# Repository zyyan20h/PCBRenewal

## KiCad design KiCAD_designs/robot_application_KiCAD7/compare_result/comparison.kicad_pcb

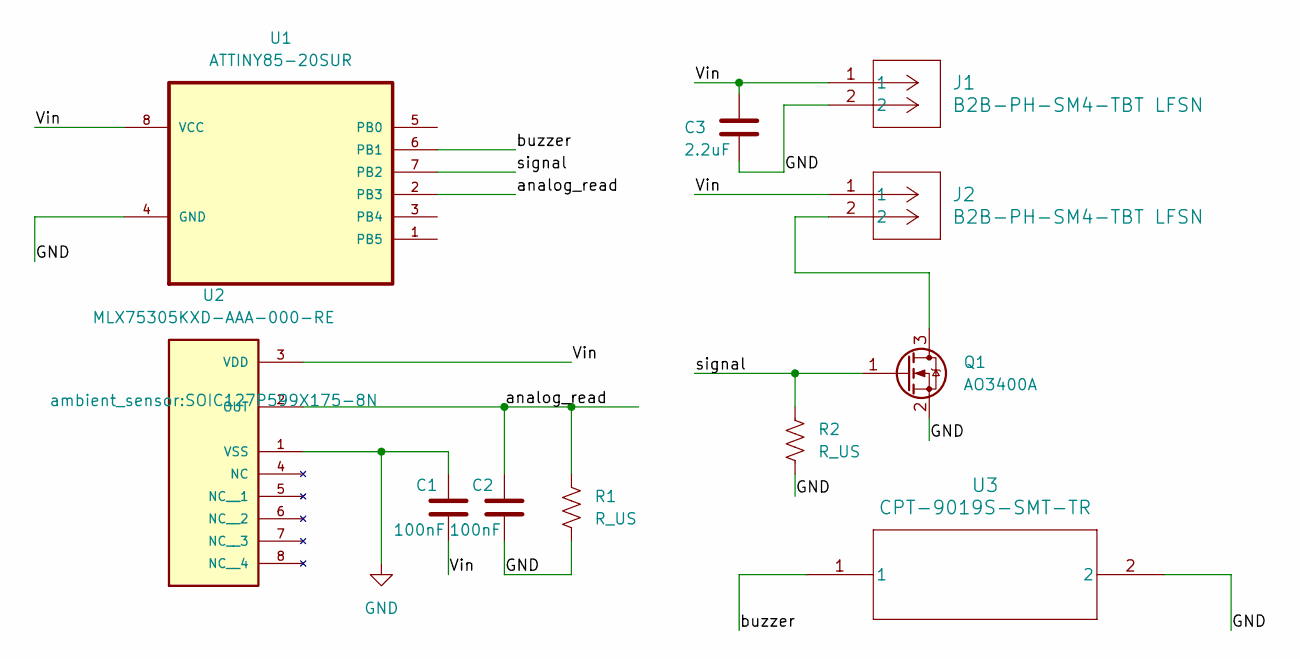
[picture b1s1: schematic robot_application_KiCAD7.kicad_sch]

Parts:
C1, C2: 100nF; C_0805_2012Metric
C3: 2.2uF; C_0805_2012Metric
J1, J2: B2B-PH-SM4-TBT LFSN; CONN2_B2B-PH-SM4_JST
Q1: AO3400A; SOT-23
R1, R2: R_US; R_0805_2012Metric
U1: ATTINY85-20SUR; MPN ATTINY85-20SUR
U2: MLX75305KXD-AAA-000-RE; SOIC127P599X175-8N; PARTREV REVISION 9 - OCTOBER 17, 2016
U3: CPT-9019S-SMT-TR; SM_CPT_9X9_CUD

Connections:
/Vin: C1.2, C3.1, J1.1, J2.1, U1.8 (VCC), U2.3 (VDD)
/analog_read: C2.1, R1.1, U1.2 (PB3), U2.2 (OUT)
/buzzer: U1.6 (PB1), U3.1
/signal: Q1.1 (G), R2.1, U1.7 (PB2)
GND: C1.1, C2.2, C3.2, J1.2, Q1.2 (S), R1.2, R2.2, U1.4 (GND), U2.1 (VSS), U3.2
unnamed: J2.2, Q1.3 (D)

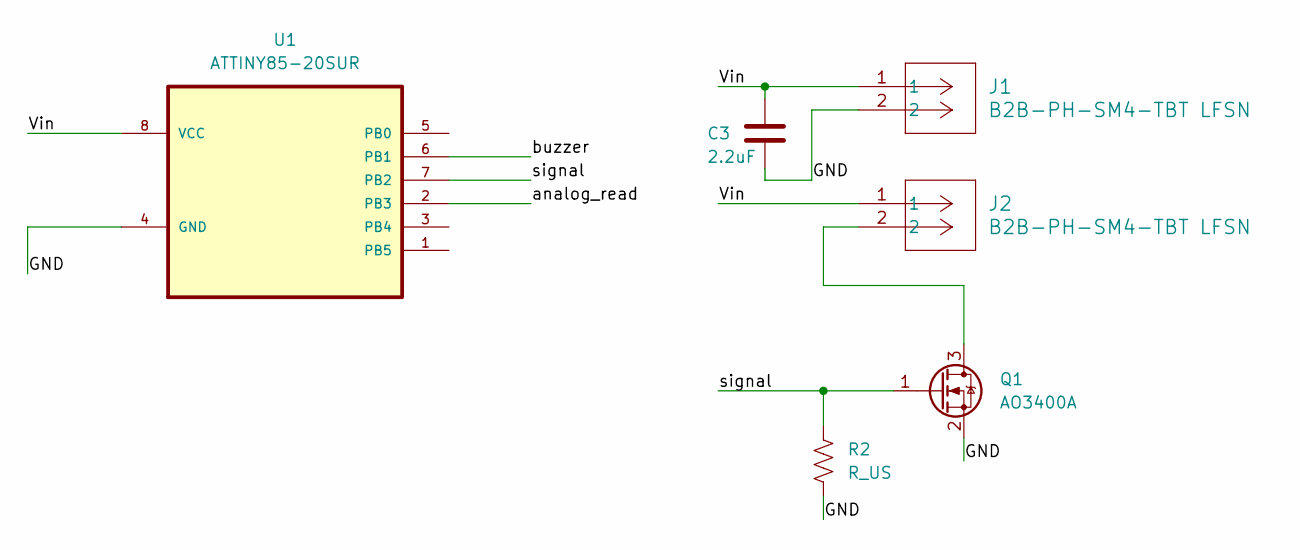
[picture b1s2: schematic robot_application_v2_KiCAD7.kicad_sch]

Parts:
C3: 2.2uF; C_0805_2012Metric
J1, J2: B2B-PH-SM4-TBT LFSN; CONN2_B2B-PH-SM4_JST
Q1: AO3400A; SOT-23
R2: R_US; R_0805_2012Metric
U1: ATTINY85-20SUR; MPN ATTINY85-20SUR

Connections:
/Vin: C3.1, J1.1, J2.1, U1.8 (VCC); also elsewhere on the board
/analog_read: U1.2 (PB3); also elsewhere on the board
/buzzer: U1.6 (PB1); also elsewhere on the board
/signal: Q1.1 (G), R2.1, U1.7 (PB2)
GND: C3.2, J1.2, Q1.2 (S), R2.2, U1.4 (GND); also elsewhere on the board
unnamed: J2.2, Q1.3 (D)

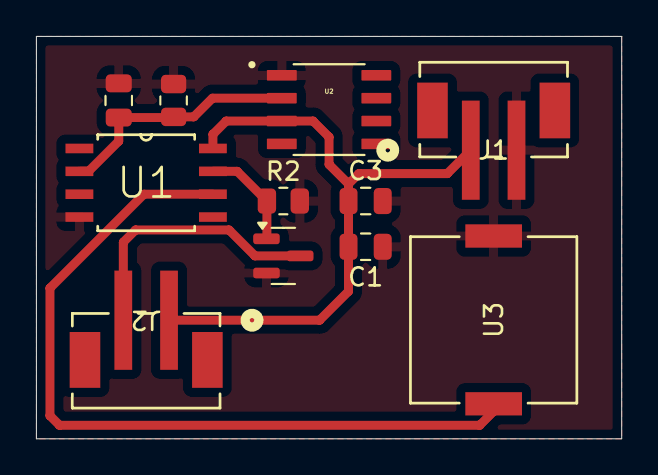
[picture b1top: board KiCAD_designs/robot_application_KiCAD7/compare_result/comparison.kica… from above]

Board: 2 copper layers, 32.5 x 22.4 mm, 11 parts (0 on the bottom side), 6 nets.

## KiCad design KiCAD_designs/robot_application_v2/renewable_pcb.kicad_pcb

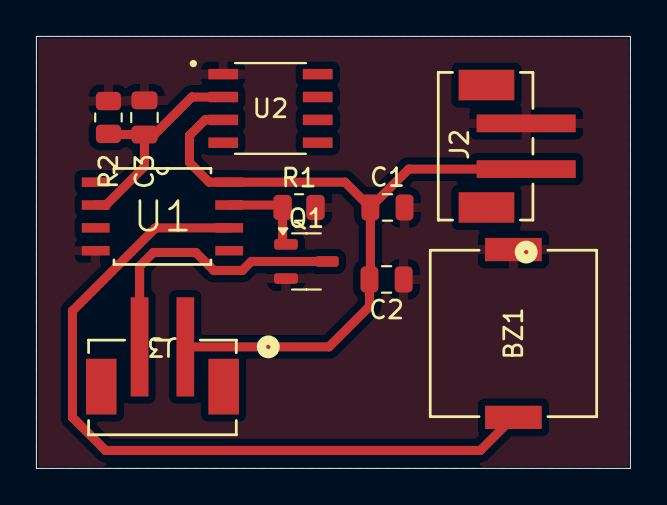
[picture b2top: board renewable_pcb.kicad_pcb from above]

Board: 2 copper layers, 33.0 x 24.0 mm, 11 parts (0 on the bottom side), 6 nets.

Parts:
BZ1: Buzzer; SM_CPT_9X9_CUD
C1: 2.2uF; C_0805_2012Metric
C2, C3: 100nF; C_0805_2012Metric
J2, J3: B2B-PH-SM4-TBT LFSN; CONN2_B2B-PH-SM4_JST
Q1: AO3400A; SOT-23-3
R1, R2: 10kOhm; R_0805_2012Metric
U1: ATTINY85-20SUR
U2: MLX75305KXD-AAA-000-RE; ambient_sensor

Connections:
/Vin: C1.1, C2.2, J2.1, J3.1, U1.8 (VCC), U2.3 (VDD)
/analog_read: C3.1, R2.1, U1.2 (PB3), U2.2 (OUT)
/buzzer: BZ1.1 (+), U1.6 (PB1)
/signal: Q1.1 (G), R1.1, U1.7 (PB2)
GND: BZ1.2 (-), C1.2, C2.1, C3.2, J2.2, Q1.2 (S), R1.2, R2.2, U1.4 (GND), U2.1 (VSS)
unnamed: J3.2, Q1.3 (D)

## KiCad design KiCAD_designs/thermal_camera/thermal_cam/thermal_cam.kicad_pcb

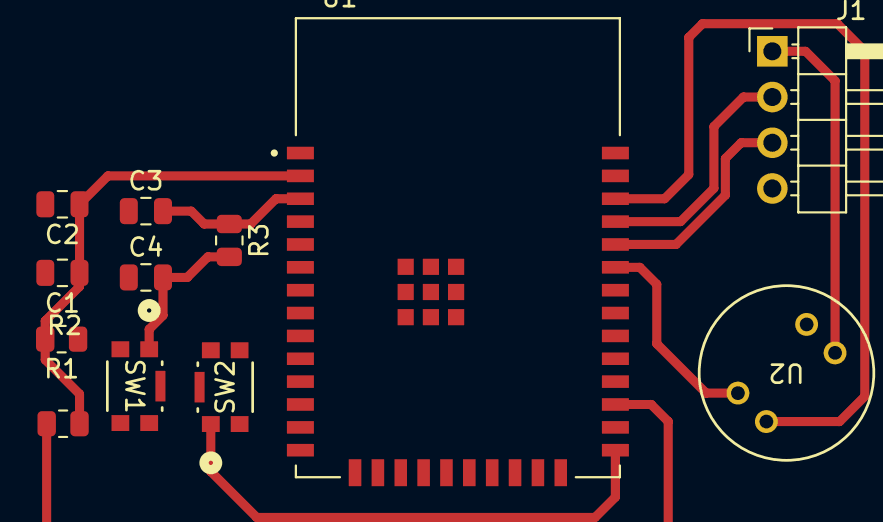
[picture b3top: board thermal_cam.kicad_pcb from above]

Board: 2 copper layers, 12 parts (0 on the bottom side), 10 nets.

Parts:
C1, C2, C3, C4: C; C_0805_2012Metric
J1: Conn_01x04_Pin; PinHeader_1x04_P2.54mm_Horizontal
R1, R2, R3: R; R_0805_2012Metric
SW1, SW2: KMR223G LFG; KMR2_G_CNK
U1: ESP32-WROOM-32E__4MB_; XCVR_ESP32-WROOM-32E__4MB_
U2: MLX90640ESF-BAB-000-TU; FOV55d_MEL

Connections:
/SCL: U1.33 (IO21), U2.4 (SCL)
/SDA: U1.36 (IO22), U2.1 (SDA)
GND: C1.2, C2.2, C3.1, C4.1, J1.4, SW1.3, SW2.3, U1.1 (GND), U1.15 (GND), U1.38 (GND), U1.39_1 (GND), U1.39_2 (GND), U1.39_3 (GND), U1.39_4 (GND), U1.39_5 (GND), U1.39_6 (GND), U1.39_7 (GND), U1.39_8 (GND), U1.39_9 (GND), U2.3 (GND)
unnamed: C4.2, R3.2, SW1.1
unnamed: J1.2, U1.35 (TXD0)
unnamed: J1.3, U1.34 (RXD0)
unnamed: C3.2, R1.1, R3.1, U1.3 (EN)
unnamed: SW2.1, U1.25 (IO0)
unnamed: R2.1, U1.27 (IO16)
VDD: C1.1, C2.1, J1.1, R1.2, R2.2, U1.2 (3V3), U2.2 (VDD)

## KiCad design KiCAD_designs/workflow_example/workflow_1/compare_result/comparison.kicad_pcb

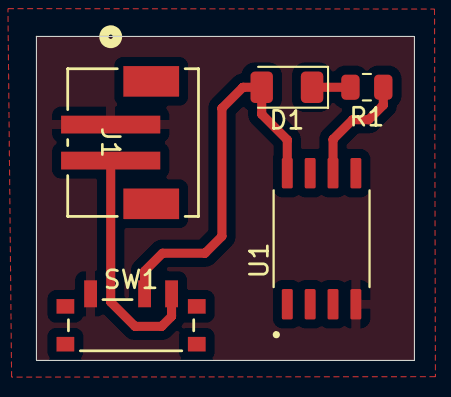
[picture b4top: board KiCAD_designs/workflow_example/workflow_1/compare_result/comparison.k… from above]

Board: 2 copper layers, 21.0 x 18.0 mm, 5 parts (0 on the bottom side), 5 nets.

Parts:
D1: LED; LED_1206_3216Metric
J1: B2B-PH-SM4-TBLFSN; B2B-PH-SM4-TBLFSN_JST
R1: R; R_0805_2012Metric
SW1: CUS-12TB; CUS-12TB_NDC
U1: ATTINY45-20SU; SOIC127P794X202-8N

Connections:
/GND: J1.1, SW1.1, U1.4 (GND)
/LED: R1.1, U1.6 (PB1)
/vcc: D1.2 (A), SW1.2, U1.8 (VCC)
/vin: J1.2, SW1.3
unnamed: D1.1 (K), R1.2
